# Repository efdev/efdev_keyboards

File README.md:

# PCBs

# Firmware

Based on zmk.

Basic setup see https://zmk.dev/docs/development/setup .

Extend zmk west.yml remotes list with the following 

```
- name: microsoft
      url-base: https://github.com/microsoft
```
and the projects list with
```
- name: uf2
      remote: microsoft
      path: tools/uf2
      clone-depth: 1
```
and run `west update`

Build firmware `west build -p -b <board> -- -DBOARD_ROOT=<path to cloned repo>/Firmware`

Example: `west build -p -b akortho -- -DBOARD_ROOT=/home/efdev/Documents/Keyboards/Firmware`

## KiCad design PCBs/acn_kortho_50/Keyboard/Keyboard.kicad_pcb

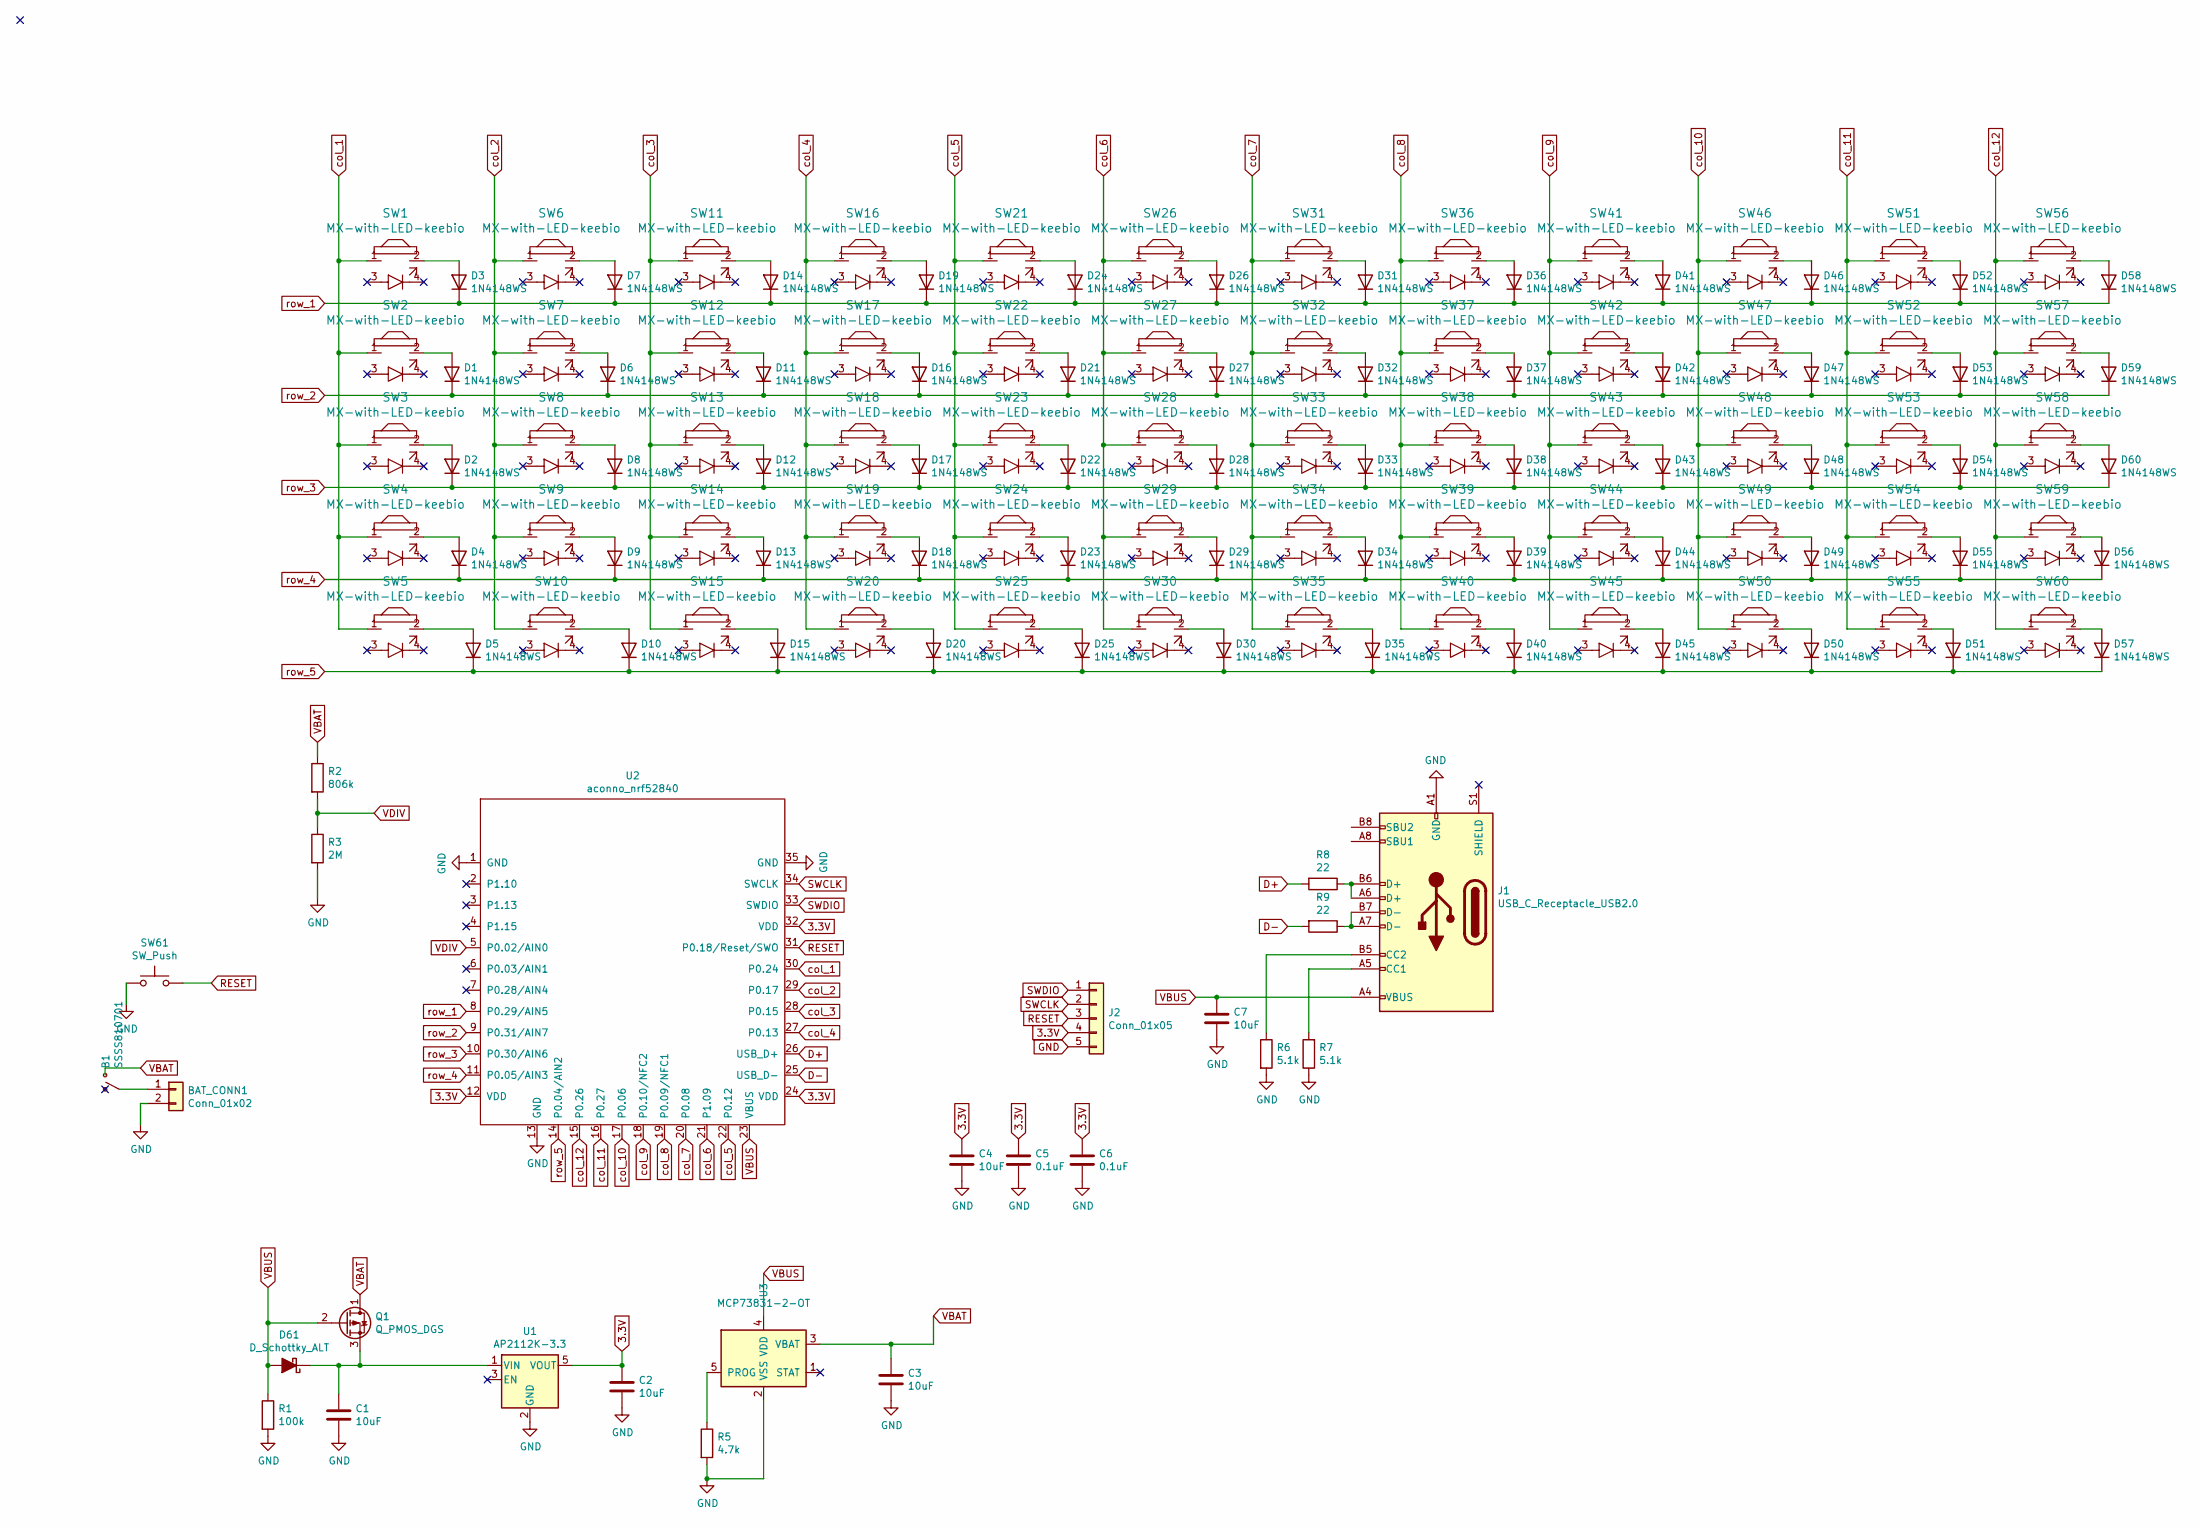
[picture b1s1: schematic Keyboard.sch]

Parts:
B1: SSSS810701
BAT_CONN1: Conn_01x02; PinHeader_1x02_P2.54mm_Vertical_SMD_Pin1Left
C1, C2, C3, C4, C7: 10uF; C_0603_1608Metric_Pad1.08x0.95mm_HandSolder
C5, C6: 0.1uF; C_0603_1608Metric_Pad1.08x0.95mm_HandSolder
D1, D2, D3, D4, D5, D6, D7, D8, D9, D10, D11, D12, D13, D14, D15, D16, D17, D18, D19, D20, D21, D22, D23, D24, D25, D26, D27, D28, D29, D30, D31, D32, D33, D34, D35, D36, D37, D38, D39, D40, D41, D42, D43, D44, D45, D46, D47, D48, D49, D50, D51, D52, D53, D54, D55, D56, D57, D58, D59, D60: 1N4148WS; D_SOD-323_HandSoldering
D61: D_Schottky_ALT; D_SOD-123F
J1: USB_C_Receptacle_USB2.0; USB_C_Receptacle_GCT_USB4085
J2: Conn_01x05; SWD
Q1: Q_PMOS_DGS; SOT-23_Handsoldering
R1: 100k; R_0603_1608Metric_Pad0.98x0.95mm_HandSolder
R2: 806k; R_0603_1608Metric_Pad0.98x0.95mm_HandSolder
R3: 2M; R_0603_1608Metric_Pad0.98x0.95mm_HandSolder
R5: 4.7k; R_0603_1608Metric_Pad0.98x0.95mm_HandSolder
R6, R7: 5.1k; R_0603_1608Metric_Pad0.98x0.95mm_HandSolder
R8, R9: 22; R_0603_1608Metric_Pad0.98x0.95mm_HandSolder
SW1, SW2, SW3, SW4, SW5, SW6, SW7, SW8, SW9, SW10, SW11, SW12, SW13, SW14, SW15, SW16, SW17, SW18, SW19, SW20, SW21, SW22, SW23, SW24, SW25, SW26, SW27, SW28, SW29, SW30, SW31, SW32, SW33, SW34, SW35, SW36, SW37, SW38, SW39, SW40, SW41, SW42, SW43, SW44, SW45, SW46, SW47, SW48, SW49, SW50, SW51, SW52, SW53, SW54, SW55, SW56, SW57, SW58, SW59, SW60: MX-with-LED-keebio; SW_Cherry_MX_1.00u_PCB
SW61: SW_Push; SW_Push_1P1T_NO_6x6mm_H9.5mm
U1: AP2112K-3.3; SOT-223
U2: aconno_nrf52840; aconno_nrf_52840_tht
U3: MCP73831-2-OT; SOT-23-5_HandSoldering

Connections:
3.3V: C2.1, C4.1, C5.1, C6.1, J2.4, U1.5 (VOUT), U2.12 (VDD), U2.24 (VDD), U2.32 (VDD)
D+: R8.2, U2.26 (USB_D+)
D-: R9.2, U2.25 (USB_D-)
GND: BAT_CONN1.2, C1.2, C2.2, C3.2, C4.2, C5.2, C6.2, C7.2, J1.A1 (GND), J1.A12 (GND), J1.B1 (GND), J1.B12 (GND), J1.S1 (SHIELD), J2.5, R1.2, R3.2, R5.2, R6.2, R7.1, SW61.1, U1.2 (GND), U2.1 (GND), U2.13 (GND), U2.35 (GND), U3.2 (VSS)
unnamed: B1.2, BAT_CONN1.1
unnamed: C1.1, D61.1 (K), Q1.3 (S), U1.1 (VIN)
unnamed: D1.2 (A), SW2.2
unnamed: D2.2 (A), SW3.2
unnamed: D3.2 (A), SW1.2
unnamed: D4.2 (A), SW4.2
unnamed: D5.2 (A), SW5.2
unnamed: D6.2 (A), SW7.2
unnamed: D7.2 (A), SW6.2
unnamed: D8.2 (A), SW8.2
unnamed: D9.2 (A), SW9.2
unnamed: D10.2 (A), SW10.2
unnamed: D11.2 (A), SW12.2
unnamed: D12.2 (A), SW13.2
unnamed: D13.2 (A), SW14.2
unnamed: D14.2 (A), SW11.2
unnamed: D15.2 (A), SW15.2
unnamed: D16.2 (A), SW17.2
unnamed: D17.2 (A), SW18.2
unnamed: D18.2 (A), SW19.2
unnamed: D19.2 (A), SW16.2
unnamed: D20.2 (A), SW20.2
unnamed: D21.2 (A), SW22.2
unnamed: D22.2 (A), SW23.2
unnamed: D23.2 (A), SW24.2
unnamed: D24.2 (A), SW21.2
unnamed: D25.2 (A), SW25.2
unnamed: D26.2 (A), SW26.2
unnamed: D27.2 (A), SW27.2
unnamed: D28.2 (A), SW28.2
unnamed: D29.2 (A), SW29.2
unnamed: D30.2 (A), SW30.2
unnamed: D31.2 (A), SW31.2
unnamed: D32.2 (A), SW32.2
unnamed: D33.2 (A), SW33.2
unnamed: D34.2 (A), SW34.2
unnamed: D35.2 (A), SW35.2
unnamed: D36.2 (A), SW36.2
unnamed: D37.2 (A), SW37.2
unnamed: D38.2 (A), SW38.2
unnamed: D39.2 (A), SW39.2
unnamed: D40.2 (A), SW40.2
unnamed: D41.2 (A), SW41.2
unnamed: D42.2 (A), SW42.2
unnamed: D43.2 (A), SW43.2
unnamed: D44.2 (A), SW44.2
unnamed: D45.2 (A), SW45.2
unnamed: D46.2 (A), SW46.2
unnamed: D47.2 (A), SW47.2
unnamed: D48.2 (A), SW48.2
unnamed: D49.2 (A), SW49.2
unnamed: D50.2 (A), SW50.2
unnamed: D51.2 (A), SW55.2
unnamed: D52.2 (A), SW51.2
unnamed: D53.2 (A), SW52.2
unnamed: D54.2 (A), SW53.2
unnamed: D55.2 (A), SW54.2
unnamed: D56.2 (A), SW59.2
unnamed: D57.2 (A), SW60.2
unnamed: D58.2 (A), SW56.2
unnamed: D59.2 (A), SW57.2
unnamed: D60.2 (A), SW58.2
unnamed: J1.A5 (CC1), R7.2
unnamed: J1.A6 (D+), J1.B6 (D+), R8.1
unnamed: J1.A7 (D-), J1.B7 (D-), R9.1
unnamed: J1.B5 (CC2), R6.1
unnamed: R5.1, U3.5 (PROG)
RESET: J2.3, SW61.2, U2.31 (P0.18/Reset/SWO)
SWCLK: J2.2, U2.34 (SWCLK)
SWDIO: J2.1, U2.33 (SWDIO)
VBAT: B1.1, C3.1, Q1.1 (D), R2.1, U3.3 (VBAT)
VBUS: C7.1, D61.2 (A), J1.A4 (VBUS), J1.A9 (VBUS), J1.B4 (VBUS), J1.B9 (VBUS), Q1.2 (G), R1.1, U2.23 (VBUS), U3.4 (VDD)
VDIV: R2.2, R3.1, U2.5 (P0.02/AIN0)
col_1: SW1.1, SW2.1, SW3.1, SW4.1, SW5.1, U2.30 (P0.24)
col_2: SW6.1, SW7.1, SW8.1, SW9.1, SW10.1, U2.29 (P0.17)
col_3: SW11.1, SW12.1, SW13.1, SW14.1, SW15.1, U2.28 (P0.15)
col_4: SW16.1, SW17.1, SW18.1, SW19.1, SW20.1, U2.27 (P0.13)
col_5: SW21.1, SW22.1, SW23.1, SW24.1, SW25.1, U2.22 (P0.12)
col_6: SW26.1, SW27.1, SW28.1, SW29.1, SW30.1, U2.21 (P1.09)
col_7: SW31.1, SW32.1, SW33.1, SW34.1, SW35.1, U2.20 (P0.08)
col_8: SW36.1, SW37.1, SW38.1, SW39.1, SW40.1, U2.19 (P0.09/NFC1)
col_9: SW41.1, SW42.1, SW43.1, SW44.1, SW45.1, U2.18 (P0.10/NFC2)
col_10: SW46.1, SW47.1, SW48.1, SW49.1, SW50.1, U2.17 (P0.06)
col_11: SW51.1, SW52.1, SW53.1, SW54.1, SW55.1, U2.16 (P0.27)
col_12: SW56.1, SW57.1, SW58.1, SW59.1, SW60.1, U2.15 (P0.26)
row_1: D3.1 (K), D7.1 (K), D14.1 (K), D19.1 (K), D24.1 (K), D26.1 (K), D31.1 (K), D36.1 (K), D41.1 (K), D46.1 (K), D52.1 (K), D58.1 (K), U2.8 (P0.29/AIN5)
row_2: D1.1 (K), D6.1 (K), D11.1 (K), D16.1 (K), D21.1 (K), D27.1 (K), D32.1 (K), D37.1 (K), D42.1 (K), D47.1 (K), D53.1 (K), D59.1 (K), U2.9 (P0.31/AIN7)
row_3: D2.1 (K), D8.1 (K), D12.1 (K), D17.1 (K), D22.1 (K), D28.1 (K), D33.1 (K), D38.1 (K), D43.1 (K), D48.1 (K), D54.1 (K), D60.1 (K), U2.10 (P0.30/AIN6)
row_4: D4.1 (K), D9.1 (K), D13.1 (K), D18.1 (K), D23.1 (K), D29.1 (K), D34.1 (K), D39.1 (K), D44.1 (K), D49.1 (K), D55.1 (K), D56.1 (K), U2.11 (P0.05/AIN3)
row_5: D5.1 (K), D10.1 (K), D15.1 (K), D20.1 (K), D25.1 (K), D30.1 (K), D35.1 (K), D40.1 (K), D45.1 (K), D50.1 (K), D51.1 (K), D57.1 (K), U2.14 (P0.04/AIN2)

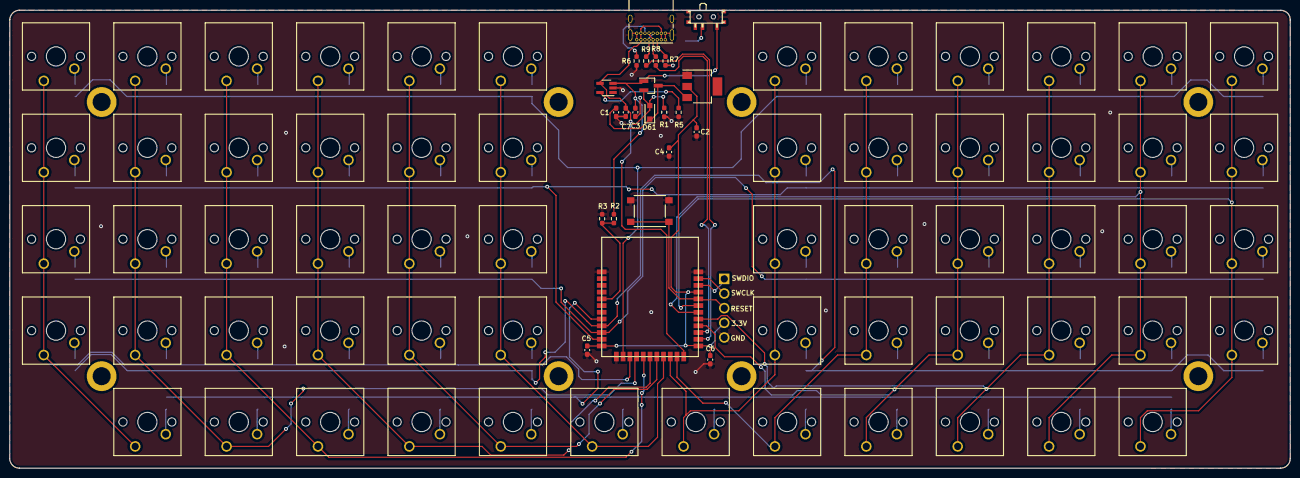
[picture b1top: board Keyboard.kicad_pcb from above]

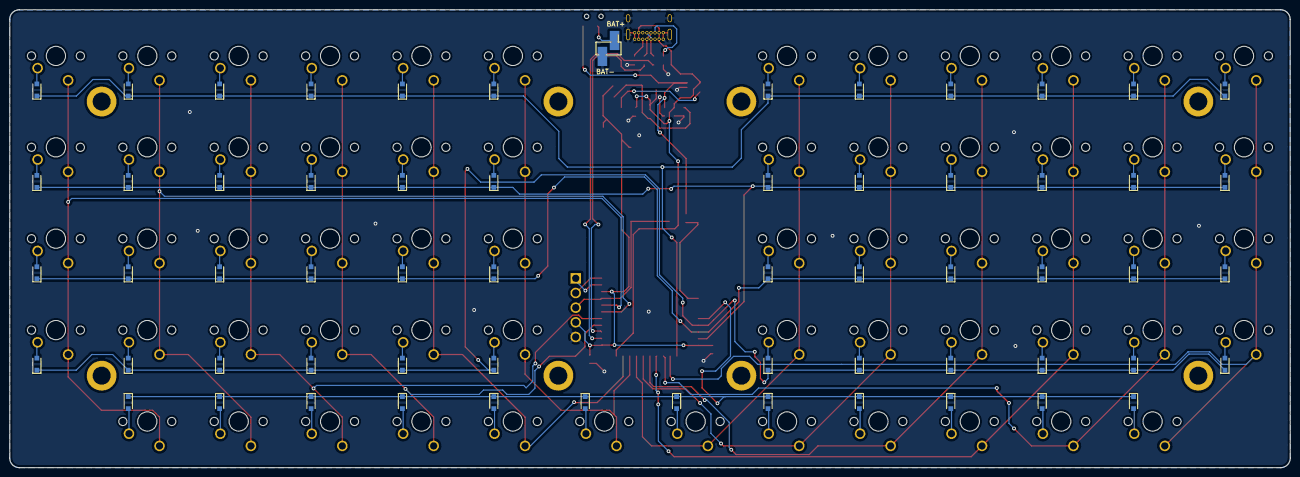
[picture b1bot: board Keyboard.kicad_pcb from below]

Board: 2 copper layers, 266.2 x 95.2 mm, 145 parts (61 on the bottom side), 94 nets.

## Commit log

2020-11-21 added backplate
2020-11-21 added plate
2020-11-21 added keyboard
2020-11-21 changed footprint reference
2021-05-25 some stuff
2022-06-18 Added board config
